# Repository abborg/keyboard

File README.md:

Keyboard
========

This repository is dedicated to information and the process of constructing my own custom mechanical keyboard. The hope is that this will be used to store my own notes and layout for future use or modification.

## Layout  

The layout is a unique design I have developed after studying other popular layouts. It has yet to be tested and will require a fair amount of getting used to compared to other layouts. It attempts to utilize the Workman layout and reduce the size of modifier keys. The layout was designed with intuition in mind. As such, much of the layout is symmetrical in an attempt to provide a regular structure to the placement of non-alphabet keys. The idea behind this is that one can make a good guess of where a symbol key is based upon the location of similar keys. Working with a keyboard with access to the microcontroller allows for the layout to be adjusted to suite the needs of the user. 

<sub>[View Layout](http://www.keyboard-layout-editor.com/#/gists/b67145701f86c79b1c43)</sub>  

Inspired by:
------------

Jack Humbert, of [Ortholinear Keyboards](www.ortholinearkeyboards.com)

Will Yager, with his [MicroMechBoard](http://yager.io/keyboard/keyboard.html)

The members of [r/olkb](http://www.reddit.com/r/olkb)

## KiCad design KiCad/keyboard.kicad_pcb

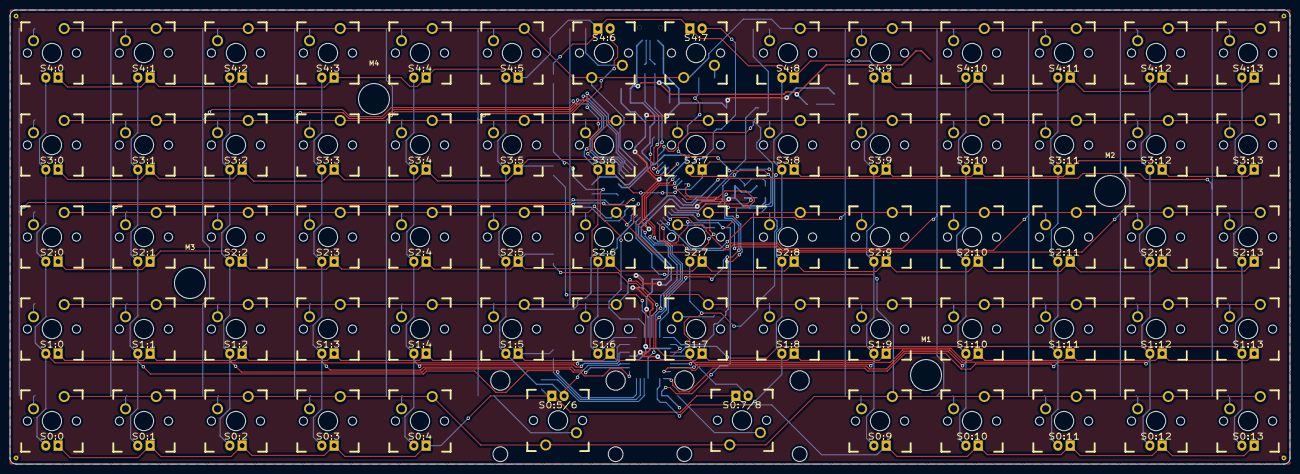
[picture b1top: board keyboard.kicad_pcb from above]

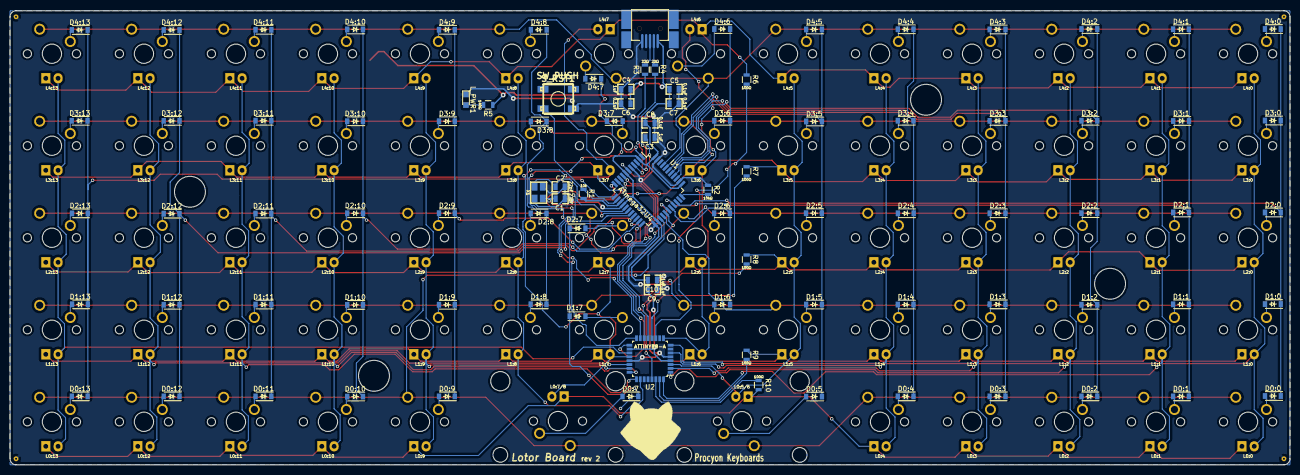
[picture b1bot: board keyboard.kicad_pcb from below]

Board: 2 copper layers, 265.0 x 94.0 mm, 239 parts (96 on the bottom side), 128 nets.

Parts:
C1, C2: 22pF; 0805C
C3, C4: 1uF; 0805C
C5, C6, C7, C8, C9, C10: 0.1uF; 0805C
D0:0, D0:1, D0:2, D0:3, D0:4, D0:5, D0:7, D0:9, D0:10, D0:11, D0:12, D0:13, D1:0, D1:1, D1:2, D1:3, D1:4, D1:5, D1:6, D1:7, D1:8, D1:9, D1:10, D1:11, D1:12, D1:13, D2:0, D2:1, D2:2, D2:3, D2:4, D2:5, D2:6, D2:7, D2:8, D2:9, D2:10, D2:11, D2:12, D2:13, D3:0, D3:1, D3:2, D3:3, D3:4, D3:5, D3:6, D3:7, D3:8, D3:9, D3:10, D3:11, D3:12, D3:13, D4:0, D4:1, D4:2, D4:3, D4:4, D4:5, D4:6, D4:7, D4:8, D4:9, D4:10, D4:11, D4:12, D4:13: D; SOD-123D
G2: LOGO; racc1
J1: USBMINI_B05; USB_MINI-B-67503
L0:0, L0:1, L0:2, L0:3, L0:4, L0:5/6, L0:7/8, L0:9, L0:10, L0:11, L0:12, L0:13, L1:0, L1:1, L1:2, L1:3, L1:4, L1:5, L1:6, L1:7, L1:8, L1:9, L1:10, L1:11, L1:12, L1:13, L2:0, L2:1, L2:2, L2:3, L2:4, L2:5, L2:6, L2:7, L2:8, L2:9, L2:10, L2:11, L2:12, L2:13, L3:0, L3:1, L3:2, L3:3, L3:4, L3:5, L3:6, L3:7, L3:8, L3:9, L3:10, L3:11, L3:12, L3:13, L4:0, L4:1, L4:2, L4:3, L4:4, L4:5, L4:6, L4:7, L4:8, L4:9, L4:10, L4:11, L4:12, L4:13: LED; CHERRY_MX_LED
L_PWR1: LED; 0805L
M1, M2, M3, M4: MountingHole_6.4mm; MountingHole_6.4mm_M6
R1: 10k; 0805R
R2: 10kΩ; 0805R
R3, R4: 22Ω; 0805R
R5: 140Ω; 0805R
R6, R7, R8, R9, R10: 100Ω; 0805R
S0:0, S0:1, S0:2, S0:3, S0:4, S0:9, S0:10, S0:11, S0:12, S0:13, S1:0, S1:1, S1:2, S1:3, S1:4, S1:5, S1:6, S1:7, S1:8, S1:9, S1:10, S1:11, S1:12, S1:13, S2:0, S2:1, S2:2, S2:3, S2:4, S2:5, S2:6, S2:7, S2:8, S2:9, S2:10, S2:11, S2:12, S2:13, S3:0, S3:1, S3:2, S3:3, S3:4, S3:5, S3:6, S3:7, S3:8, S3:9, S3:10, S3:11, S3:12, S3:13, S4:0, S4:1, S4:2, S4:3, S4:4, S4:5, S4:6, S4:7, S4:8, S4:9, S4:10, S4:11, S4:12, S4:13: SW_PUSH; CHERRY_PCB_100H
S0:5/6, S0:7/8: SW_PUSH; CHERRY_PCB_200H
S_RST1: SW_PUSH; DTSJW-66N
T1, T2, T3, T4: CONN_1; pad
U1: ATmega32U4; ATmega32u4
U2: ATTINY88-A; ATtiny88
X1: CRYSTAL(4pin); Crystal-4pad

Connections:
/led/lcol0: L0:0.2, L1:0.2, L2:0.2, L3:0.2, L4:0.2, U2.8
/led/lcol1: L0:1.2, L1:1.2, L2:1.2, L3:1.2, L4:1.2, U2.32
/led/lcol2: L0:2.2, L1:2.2, L2:2.2, L3:2.2, L4:2.2, U2.1
/led/lcol3: L0:3.2, L1:3.2, L2:3.2, L3:3.2, L4:3.2, U2.2
/led/lcol4: L0:4.2, L1:4.2, L2:4.2, L3:4.2, L4:4.2, U2.6
/led/lcol5: L0:5/6.2, L1:5.2, L2:5.2, L3:5.2, L4:5.2, U2.3
/led/lcol6: L1:6.2, L2:6.2, L3:6.2, L4:6.2, U2.9
/led/lcol7: L0:7/8.2, L1:7.2, L2:7.2, L3:7.2, L4:7.2, U2.20
/led/lcol8: L1:8.2, L2:8.2, L3:8.2, L4:8.2, U2.26
/led/lcol9: L0:9.2, L1:9.2, L2:9.2, L3:9.2, L4:9.2, U2.23
/led/lcol10: L0:10.2, L1:10.2, L2:10.2, L3:10.2, L4:10.2, U2.24
/led/lcol11: L0:11.2, L1:11.2, L2:11.2, L3:11.2, L4:11.2, U2.25
/led/lcol12: L0:12.2, L1:12.2, L2:12.2, L3:12.2, L4:12.2, U2.22
/led/lcol13: L0:13.2, L1:13.2, L2:13.2, L3:13.2, L4:13.2, U2.19
/led/lrow0: R10.2, U2.30
/led/lrow1: R9.2, U2.31
/led/lrow2: R8.2, U2.13
/led/lrow3: R7.2, U2.12
/led/lrow4: R6.2, U2.11
/led/miso: U1.11, U2.16
/led/mosi: U1.10, U2.15
/led/sck: U1.9, U2.17
/led/~reset~: U1.28, U2.29
/led/~ss~: U1.8, U2.14
/matrix/col0: D0:0.1, D1:0.1, D2:0.1, D3:0.1, D4:0.1, U1.31
/matrix/col1: D0:1.1, D1:1.1, D2:1.1, D3:1.1, D4:1.1, U1.30
/matrix/col2: D0:2.1, D1:2.1, D2:2.1, D3:2.1, D4:2.1, U1.37
/matrix/col3: D0:3.1, D1:3.1, D2:3.1, D3:3.1, D4:3.1, U1.38
/matrix/col4: D0:4.1, D1:4.1, D2:4.1, D3:4.1, D4:4.1, U1.39
/matrix/col5: D0:5.1, D1:5.1, D2:5.1, D3:5.1, D4:5.1, U1.40
/matrix/col6: D1:6.1, D2:6.1, D3:6.1, D4:6.1, U1.29
/matrix/col7: D0:7.1, D1:7.1, D2:7.1, D3:7.1, D4:7.1, U1.22
/matrix/col8: D1:8.1, D2:8.1, D3:8.1, D4:8.1, U1.1
/matrix/col9: D0:9.1, D1:9.1, D2:9.1, D3:9.1, D4:9.1, U1.21
/matrix/col10: D0:10.1, D1:10.1, D2:10.1, D3:10.1, D4:10.1, U1.20
/matrix/col11: D0:11.1, D1:11.1, D2:11.1, D3:11.1, D4:11.1, U1.19
/matrix/col12: D0:12.1, D1:12.1, D2:12.1, D3:12.1, D4:12.1, U1.18
/matrix/col13: D0:13.1, D1:13.1, D2:13.1, D3:13.1, D4:13.1, U1.12
/matrix/row0: S0:0.1, S0:1.1, S0:2.1, S0:3.1, S0:4.1, S0:5/6.1, S0:7/8.1, S0:9.1, S0:10.1, S0:11.1, S0:12.1, S0:13.1, U1.25
/matrix/row1: S1:0.1, S1:1.1, S1:2.1, S1:3.1, S1:4.1, S1:5.1, S1:6.1, S1:7.1, S1:8.1, S1:9.1, S1:10.1, S1:11.1, S1:12.1, S1:13.1, U1.26
/matrix/row2: S2:0.1, S2:1.1, S2:2.1, S2:3.1, S2:4.1, S2:5.1, S2:6.1, S2:7.1, S2:8.1, S2:9.1, S2:10.1, S2:11.1, S2:12.1, S2:13.1, U1.27
/matrix/row3: S3:0.1, S3:1.1, S3:2.1, S3:3.1, S3:4.1, S3:5.1, S3:6.1, S3:7.1, S3:8.1, S3:9.1, S3:10.1, S3:11.1, S3:12.1, S3:13.1, U1.36
/matrix/row4: S4:0.1, S4:1.1, S4:2.1, S4:3.1, S4:4.1, S4:5.1, S4:6.1, S4:7.1, S4:8.1, S4:9.1, S4:10.1, S4:11.1, S4:12.1, S4:13.1, U1.41
/~RES~: R1.2, S_RST1.2, U1.13
GND: C1.2, C2.2, C3.2, C4.2, C5.2, C6.2, C7.2, C8.2, C9.2, C10.2, J1.5, L_PWR1.1, R2.1, S_RST1.1, T1.1, T2.1, T3.1, T4.1, U1.5, U1.15, U1.23, U1.35, U1.43, U2.5, U2.21, X1.2, X1.4
unnamed: C1.1, U1.17, X1.1
unnamed: C2.1, U1.16, X1.3
unnamed: C3.1, U1.6
unnamed: D0:0.2, S0:0.2
unnamed: D0:1.2, S0:1.2
unnamed: D0:2.2, S0:2.2
unnamed: D0:3.2, S0:3.2
unnamed: D0:4.2, S0:4.2
unnamed: D0:5.2, S0:5/6.2
unnamed: D0:7.2, S0:7/8.2
unnamed: D0:9.2, S0:9.2
unnamed: D0:10.2, S0:10.2
unnamed: D0:11.2, S0:11.2
unnamed: D0:12.2, S0:12.2
unnamed: D0:13.2, S0:13.2
unnamed: D1:0.2, S1:0.2
unnamed: D1:1.2, S1:1.2
unnamed: D1:2.2, S1:2.2
unnamed: D1:3.2, S1:3.2
unnamed: D1:4.2, S1:4.2
unnamed: D1:5.2, S1:5.2
unnamed: D1:6.2, S1:6.2
unnamed: D1:7.2, S1:7.2
unnamed: D1:8.2, S1:8.2
unnamed: D1:9.2, S1:9.2
unnamed: D1:10.2, S1:10.2
unnamed: D1:11.2, S1:11.2
unnamed: D1:12.2, S1:12.2
unnamed: D1:13.2, S1:13.2
unnamed: D2:0.2, S2:0.2
unnamed: D2:1.2, S2:1.2
unnamed: D2:2.2, S2:2.2
unnamed: D2:3.2, S2:3.2
unnamed: D2:4.2, S2:4.2
unnamed: D2:5.2, S2:5.2
unnamed: D2:6.2, S2:6.2
unnamed: D2:7.2, S2:7.2
unnamed: D2:8.2, S2:8.2
unnamed: D2:9.2, S2:9.2
unnamed: D2:10.2, S2:10.2
unnamed: D2:11.2, S2:11.2
unnamed: D2:12.2, S2:12.2
unnamed: D2:13.2, S2:13.2
unnamed: D3:0.2, S3:0.2
unnamed: D3:1.2, S3:1.2
unnamed: D3:2.2, S3:2.2
unnamed: D3:3.2, S3:3.2
unnamed: D3:4.2, S3:4.2
unnamed: D3:5.2, S3:5.2
unnamed: D3:6.2, S3:6.2
unnamed: D3:7.2, S3:7.2
unnamed: D3:8.2, S3:8.2
unnamed: D3:9.2, S3:9.2
unnamed: D3:10.2, S3:10.2
unnamed: D3:11.2, S3:11.2
unnamed: D3:12.2, S3:12.2
unnamed: D3:13.2, S3:13.2
unnamed: D4:0.2, S4:0.2
unnamed: D4:1.2, S4:1.2
unnamed: D4:2.2, S4:2.2
unnamed: D4:3.2, S4:3.2
unnamed: D4:4.2, S4:4.2
unnamed: D4:5.2, S4:5.2
unnamed: D4:6.2, S4:6.2
unnamed: D4:7.2, S4:7.2
unnamed: D4:8.2, S4:8.2
unnamed: D4:9.2, S4:9.2
unnamed: D4:10.2, S4:10.2
unnamed: D4:11.2, S4:11.2
unnamed: D4:12.2, S4:12.2
unnamed: D4:13.2, S4:13.2
unnamed: J1.2, R4.2
unnamed: J1.3, R3.2
unnamed: L0:0.1, L0:1.1, L0:2.1, L0:3.1, L0:4.1, L0:5/6.1, L0:7/8.1, L0:9.1, L0:10.1, L0:11.1, L0:12.1, L0:13.1, R10.1
unnamed: L1:0.1, L1:1.1, L1:2.1, L1:3.1, L1:4.1, L1:5.1, L1:6.1, L1:7.1, L1:8.1, L1:9.1, L1:10.1, L1:11.1, L1:12.1, L1:13.1, R9.1
unnamed: L2:0.1, L2:1.1, L2:2.1, L2:3.1, L2:4.1, L2:5.1, L2:6.1, L2:7.1, L2:8.1, L2:9.1, L2:10.1, L2:11.1, L2:12.1, L2:13.1, R8.1
unnamed: L3:0.1, L3:1.1, L3:2.1, L3:3.1, L3:4.1, L3:5.1, L3:6.1, L3:7.1, L3:8.1, L3:9.1, L3:10.1, L3:11.1, L3:12.1, L3:13.1, R7.1
unnamed: L4:0.1, L4:1.1, L4:2.1, L4:3.1, L4:4.1, L4:5.1, L4:6.1, L4:7.1, L4:8.1, L4:9.1, L4:10.1, L4:11.1, L4:12.1, L4:13.1, R6.1
unnamed: L_PWR1.2, R5.2
unnamed: R2.2, U1.33
unnamed: R3.1, U1.4
unnamed: R4.1, U1.3
VCC: C4.1, C5.1, C6.1, C7.1, C8.1, C9.1, C10.1, J1.1, R1.1, R5.1, U1.2, U1.7, U1.14, U1.24, U1.34, U1.44, U2.4, U2.18

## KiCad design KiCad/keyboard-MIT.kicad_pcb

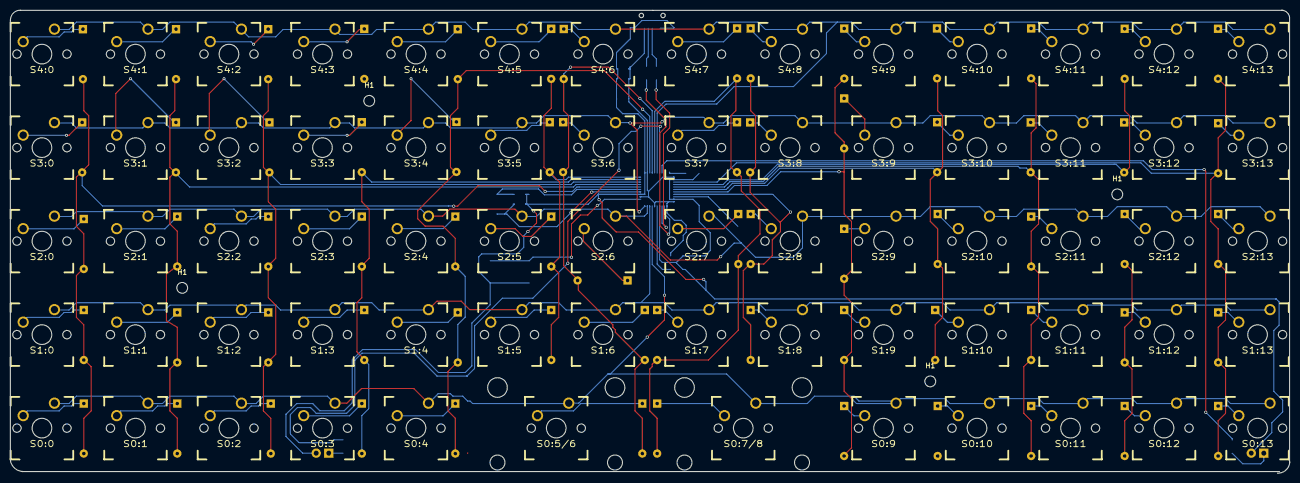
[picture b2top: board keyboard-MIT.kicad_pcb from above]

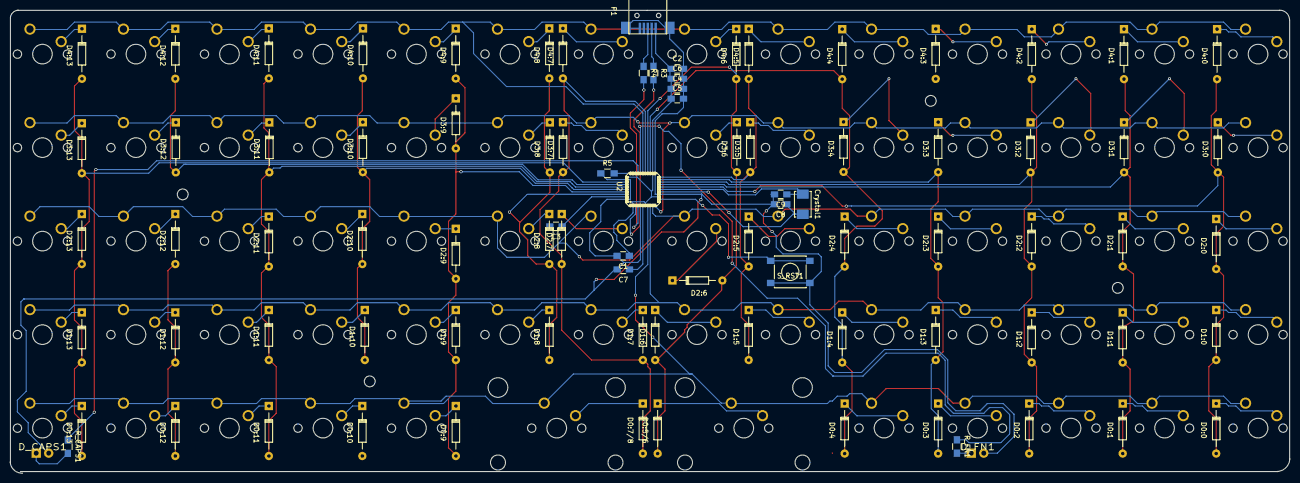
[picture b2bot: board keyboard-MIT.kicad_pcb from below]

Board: 2 copper layers, 260.0 x 94.1 mm, 160 parts (86 on the bottom side), 103 nets.

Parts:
C1, C2, C7: 1uF; C_0805_HandSoldering
C3, C4, C5, C6: 0.1uF; C_0805_HandSoldering
C8, C9: 10pF; C_0805_HandSoldering
Crystal1: 16MHz; ABM3
D0:0, D0:1, D0:2, D0:3, D0:4, D0:5/6, D0:7/8, D0:9, D0:10, D0:11, D0:12, D0:13, D1:0, D1:1, D1:2, D1:3, D1:4, D1:5, D1:6, D1:7, D1:8, D1:9, D1:10, D1:11, D1:12, D1:13, D2:0, D2:1, D2:2, D2:3, D2:4, D2:5, D2:6, D2:7, D2:8, D2:9, D2:10, D2:11, D2:12, D2:13, D3:0, D3:1, D3:2, D3:3, D3:4, D3:5, D3:6, D3:7, D3:8, D3:9, D3:10, D3:11, D3:12, D3:13, D4:0, D4:1, D4:2, D4:3, D4:4, D4:5, D4:6, D4:7, D4:8, D4:9, D4:10, D4:11, D4:12, D4:13: DIODE; Diode_DO-35_SOD27_Horizontal_RM10
D_CAPS1: LED; CHERRY_MX_LED
D_FN1: LED; CHERRY_MX_LED
H1, H1#2, H1#3, H1#4: MountingHole_2.2mm_M2
P1: USB_OTG; USB_Mini-B
R3, R4: 22; R_0805_HandSoldering
R5: 1k; R_0805_HandSoldering
R_CAPS1: RESISTOR; R_0805_HandSoldering
R_FN1: RESISTOR; R_0805_HandSoldering
S0:0, S0:1, S0:2, S0:3, S0:4, S0:9, S0:10, S0:11, S0:12, S0:13, S1:0, S1:1, S1:2, S1:3, S1:4, S1:5, S1:6, S1:7, S1:8, S1:9, S1:10, S1:11, S1:12, S1:13, S2:0, S2:1, S2:2, S2:3, S2:4, S2:5, S2:6, S2:7, S2:8, S2:9, S2:10, S2:11, S2:12, S2:13, S3:0, S3:1, S3:2, S3:3, S3:4, S3:5, S3:6, S3:7, S3:8, S3:9, S3:10, S3:11, S3:12, S3:13, S4:0, S4:1, S4:2, S4:3, S4:4, S4:5, S4:6, S4:7, S4:8, S4:9, S4:10, S4:11, S4:12, S4:13: SWITCH_PUSH; CHERRY_PCB_100H
S0:5/6, S0:7/8: SWITCH_PUSH; CHERRY_PCB_200H_U
S_RST1: SW_PUSH; SW_SPST_PTS645
U2: ATmega32U4; MLF-44_Atmel

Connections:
/COL0: D0:0.2, D1:0.2, D2:0.2, D3:0.2, D4:0.2, U2.18
/COL1: D0:1.2, D1:1.2, D2:1.2, D3:1.2, D4:1.2, U2.19
/COL2: D0:2.2, D1:2.2, D2:2.2, D3:2.2, D4:2.2, U2.20
/COL3: D0:3.2, D1:3.2, D2:3.2, D3:3.2, D4:3.2, U2.21
/COL4: D0:4.2, D1:4.2, D2:4.2, D3:4.2, D4:4.2, U2.25
/COL5: D1:5.2, D2:5.2, D3:5.2, D4:5.2, U2.22
/COL6: D0:5/6.2, D1:6.2, D2:6.2, D3:6.2, D4:6.2, U2.26
/COL7: D0:7/8.2, D1:7.2, D2:7.2, D3:7.2, D4:7.2, U2.27
/COL8: D1:8.2, D2:8.2, D3:8.2, D4:8.2, U2.41
/COL9: D0:9.2, D1:9.2, D2:9.2, D3:9.2, D4:9.2, U2.40
/COL10: D0:10.2, D1:10.2, D2:10.2, D3:10.2, D4:10.2, U2.39
/COL11: D0:11.2, D1:11.2, D2:11.2, D3:11.2, D4:11.2, U2.38
/COL12: D0:12.2, D1:12.2, D2:12.2, D3:12.2, D4:12.2, U2.37
/COL13: D0:13.2, D1:13.2, D2:13.2, D3:13.2, D4:13.2, U2.36
/LED_CAPS: R_CAPS1.1, U2.30
/LED_FN: R_FN1.1, U2.29
/ROW0: S0:0.1, S0:1.1, S0:2.1, S0:3.1, S0:4.1, S0:5/6.1, S0:7/8.1, S0:9.1, S0:10.1, S0:11.1, S0:12.1, S0:13.1, U2.8
/ROW1: S1:0.1, S1:1.1, S1:2.1, S1:3.1, S1:4.1, S1:5.1, S1:6.1, S1:7.1, S1:8.1, S1:9.1, S1:10.1, S1:11.1, S1:12.1, S1:13.1, U2.9
/ROW2: S2:0.1, S2:1.1, S2:2.1, S2:3.1, S2:4.1, S2:5.1, S2:6.1, S2:7.1, S2:8.1, S2:9.1, S2:10.1, S2:11.1, S2:12.1, S2:13.1, U2.10
/ROW3: S3:0.1, S3:1.1, S3:2.1, S3:3.1, S3:4.1, S3:5.1, S3:6.1, S3:7.1, S3:8.1, S3:9.1, S3:10.1, S3:11.1, S3:12.1, S3:13.1, U2.11
/ROW4: S4:0.1, S4:1.1, S4:2.1, S4:3.1, S4:4.1, S4:5.1, S4:6.1, S4:7.1, S4:8.1, S4:9.1, S4:10.1, S4:11.1, S4:12.1, S4:13.1, U2.28
GND: C1.2, C2.2, C4.2, C5.2, C6.2, C7.2, C8.2, C9.2, D_CAPS1.1, D_FN1.1, P1.5, P1.6, R5.1, S_RST1.1, U2.5, U2.15, U2.23, U2.35, U2.43
unnamed: C1.1, C2.1, C4.1, C5.1, C6.1, P1.1, U2.2, U2.7, U2.14, U2.24, U2.34, U2.44
unnamed: C3.1, U2.42
unnamed: C7.1, U2.6
unnamed: C8.1, Crystal1.2, U2.16
unnamed: C9.1, Crystal1.1, U2.17
unnamed: D0:0.1, S0:0.2
unnamed: D0:1.1, S0:1.2
unnamed: D0:2.1, S0:2.2
unnamed: D0:3.1, S0:3.2
unnamed: D0:4.1, S0:4.2
unnamed: D0:5/6.1, S0:5/6.2
unnamed: D0:7/8.1, S0:7/8.2
unnamed: D0:9.1, S0:9.2
unnamed: D0:10.1, S0:10.2
unnamed: D0:11.1, S0:11.2
unnamed: D0:12.1, S0:12.2
unnamed: D0:13.1, S0:13.2
unnamed: D1:0.1, S1:0.2
unnamed: D1:1.1, S1:1.2
unnamed: D1:2.1, S1:2.2
unnamed: D1:3.1, S1:3.2
unnamed: D1:4.1, S1:4.2
unnamed: D1:5.1, S1:5.2
unnamed: D1:6.1, S1:6.2
unnamed: D1:7.1, S1:7.2
unnamed: D1:8.1, S1:8.2
unnamed: D1:9.1, S1:9.2
unnamed: D1:10.1, S1:10.2
unnamed: D1:11.1, S1:11.2
unnamed: D1:12.1, S1:12.2
unnamed: D1:13.1, S1:13.2
unnamed: D2:0.1, S2:0.2
unnamed: D2:1.1, S2:1.2
unnamed: D2:2.1, S2:2.2
unnamed: D2:3.1, S2:3.2
unnamed: D2:4.1, S2:4.2
unnamed: D2:5.1, S2:5.2
unnamed: D2:6.1, S2:6.2
unnamed: D2:7.1, S2:7.2
unnamed: D2:8.1, S2:8.2
unnamed: D2:9.1, S2:9.2
unnamed: D2:10.1, S2:10.2
unnamed: D2:11.1, S2:11.2
unnamed: D2:12.1, S2:12.2
unnamed: D2:13.1, S2:13.2
unnamed: D3:0.1, S3:0.2
unnamed: D3:1.1, S3:1.2
unnamed: D3:2.1, S3:2.2
unnamed: D3:3.1, S3:3.2
unnamed: D3:4.1, S3:4.2
unnamed: D3:5.1, S3:5.2
unnamed: D3:6.1, S3:6.2
unnamed: D3:7.1, S3:7.2
unnamed: D3:8.1, S3:8.2
unnamed: D3:9.1, S3:9.2
unnamed: D3:10.1, S3:10.2
unnamed: D3:11.1, S3:11.2
unnamed: D3:12.1, S3:12.2
unnamed: D3:13.1, S3:13.2
unnamed: D4:0.1, S4:0.2
unnamed: D4:1.1, S4:1.2
unnamed: D4:2.1, S4:2.2
unnamed: D4:3.1, S4:3.2
unnamed: D4:4.1, S4:4.2
unnamed: D4:5.1, S4:5.2
unnamed: D4:6.1, S4:6.2
unnamed: D4:7.1, S4:7.2
unnamed: D4:8.1, S4:8.2
unnamed: D4:9.1, S4:9.2
unnamed: D4:10.1, S4:10.2
unnamed: D4:11.1, S4:11.2
unnamed: D4:12.1, S4:12.2
unnamed: D4:13.1, S4:13.2
unnamed: D_CAPS1.2, R_CAPS1.2
unnamed: D_FN1.2, R_FN1.2
unnamed: P1.2, R3.1
unnamed: P1.3, R4.1
unnamed: R3.2, U2.3
unnamed: R4.2, U2.4
unnamed: R5.2, U2.33
unnamed: S_RST1.2, U2.13

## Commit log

2016-01-14 Rename layout.md to layout.txt
2016-02-29 adding images, kicad, and autocad files
2016-02-29 removing old sketchup scripts
2016-04-18 pushing everything cuz i'm lazy, will cull later
2016-04-18 culling old materiasl and backup files
2016-04-18 adding gerber files
2016-04-18 updated to fix some errors
2016-04-18 removed backup file again
2016-04-19 separated grid and MIT layouts
2016-04-19 adding mit and grid layouts
2016-04-20 progress
2016-04-21 separating the different layouts
2016-05-17 changing structure
2016-05-17 updating case and adding cover
2016-05-17 adding gerber files for lotor rev 1
2016-05-31 new plate
2016-09-12 big update, got quote :(
2016-09-12 Update layout.md
    fixed link to to qwerty grid layout
2017-03-02 adding slices for acrylic 'sandwich' cases to be produced
2017-03-04 slices update
2017-03-04 new slices
2017-04-02 making revisions
2017-04-03 adding prototype for revision 3: with more support for other layouts
2017-04-03 updating rev2
2017-04-03 more updates for rev2
2017-06-19 submitting quote for case and cover
2017-06-19 create and submitted .igs files for case and cover
